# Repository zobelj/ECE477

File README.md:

# Split USB Keyboard
ECE477 Team 4 github

## Reset source code to work as keyboard
1. Make changes to .ioc file and save it
2. Build the code
3. Delete the Middlewares folder
4. Unzip Middlewares KEYBOARD SETUP.zip and rename the folder to Middlewares (Keep the ziped file here for future use)
5. Build the code (there will likely be errors, if so proceed to step 6)
6. Navigate to Drivers>STM32F4xx_HAL_DRIVER>Src in this directory there will be duplicate files that look like this `...cortex.c` and `...cortext 2.c` or `...cortex 3.c` to fix this delete all of the files that have a number at the end of the file name. This can easily be done in the console/terminal with `rm *2.c` or `rm *3.c`

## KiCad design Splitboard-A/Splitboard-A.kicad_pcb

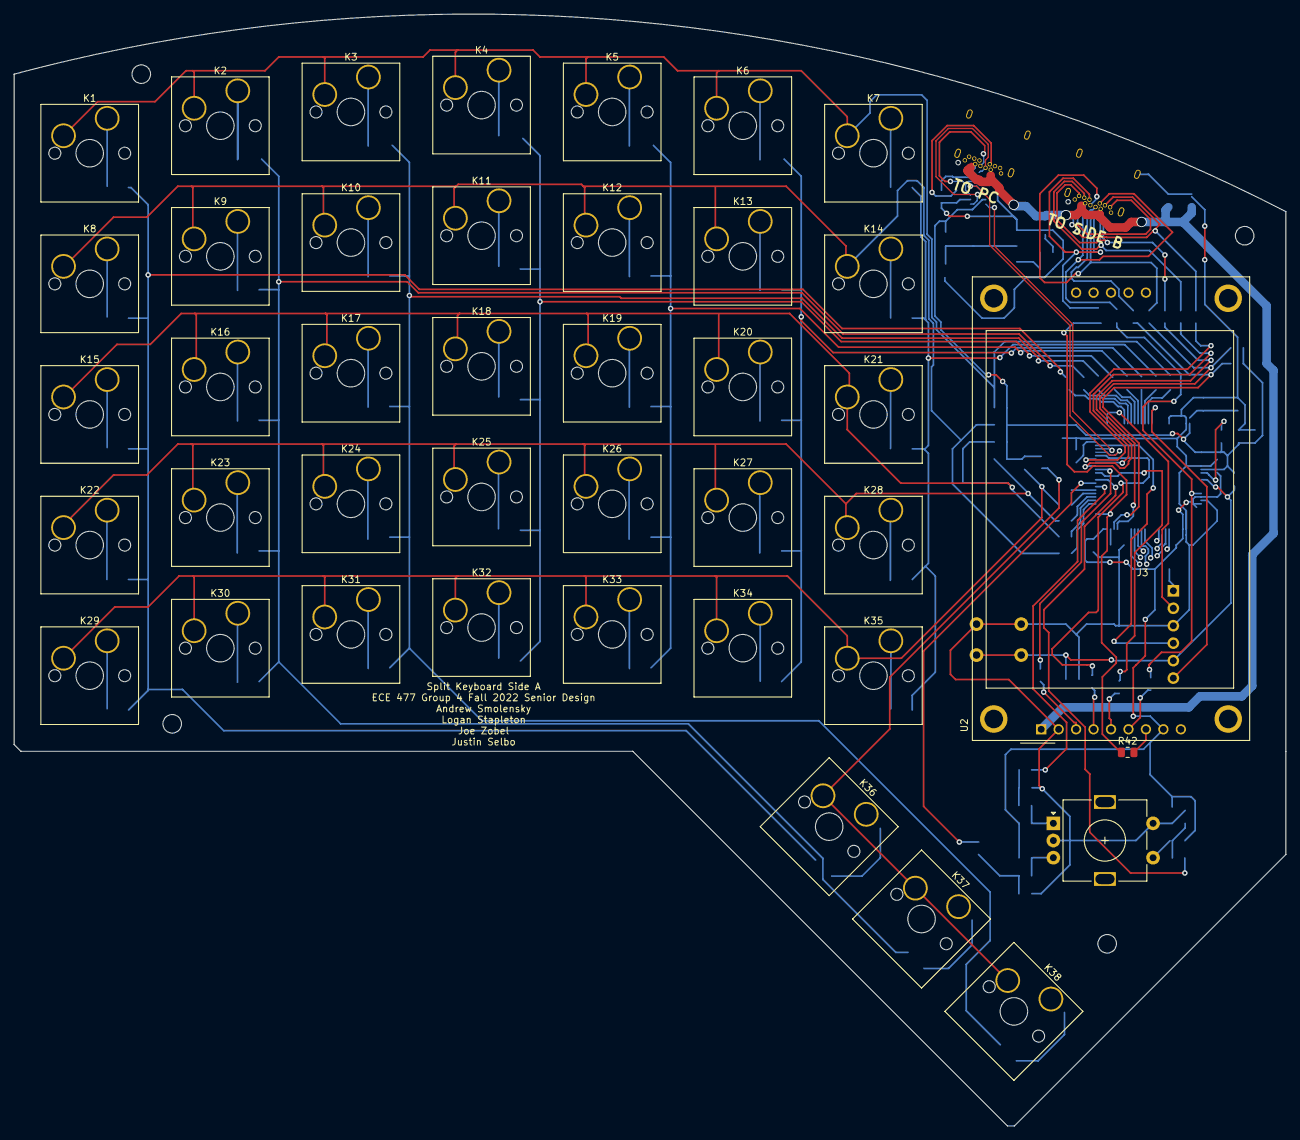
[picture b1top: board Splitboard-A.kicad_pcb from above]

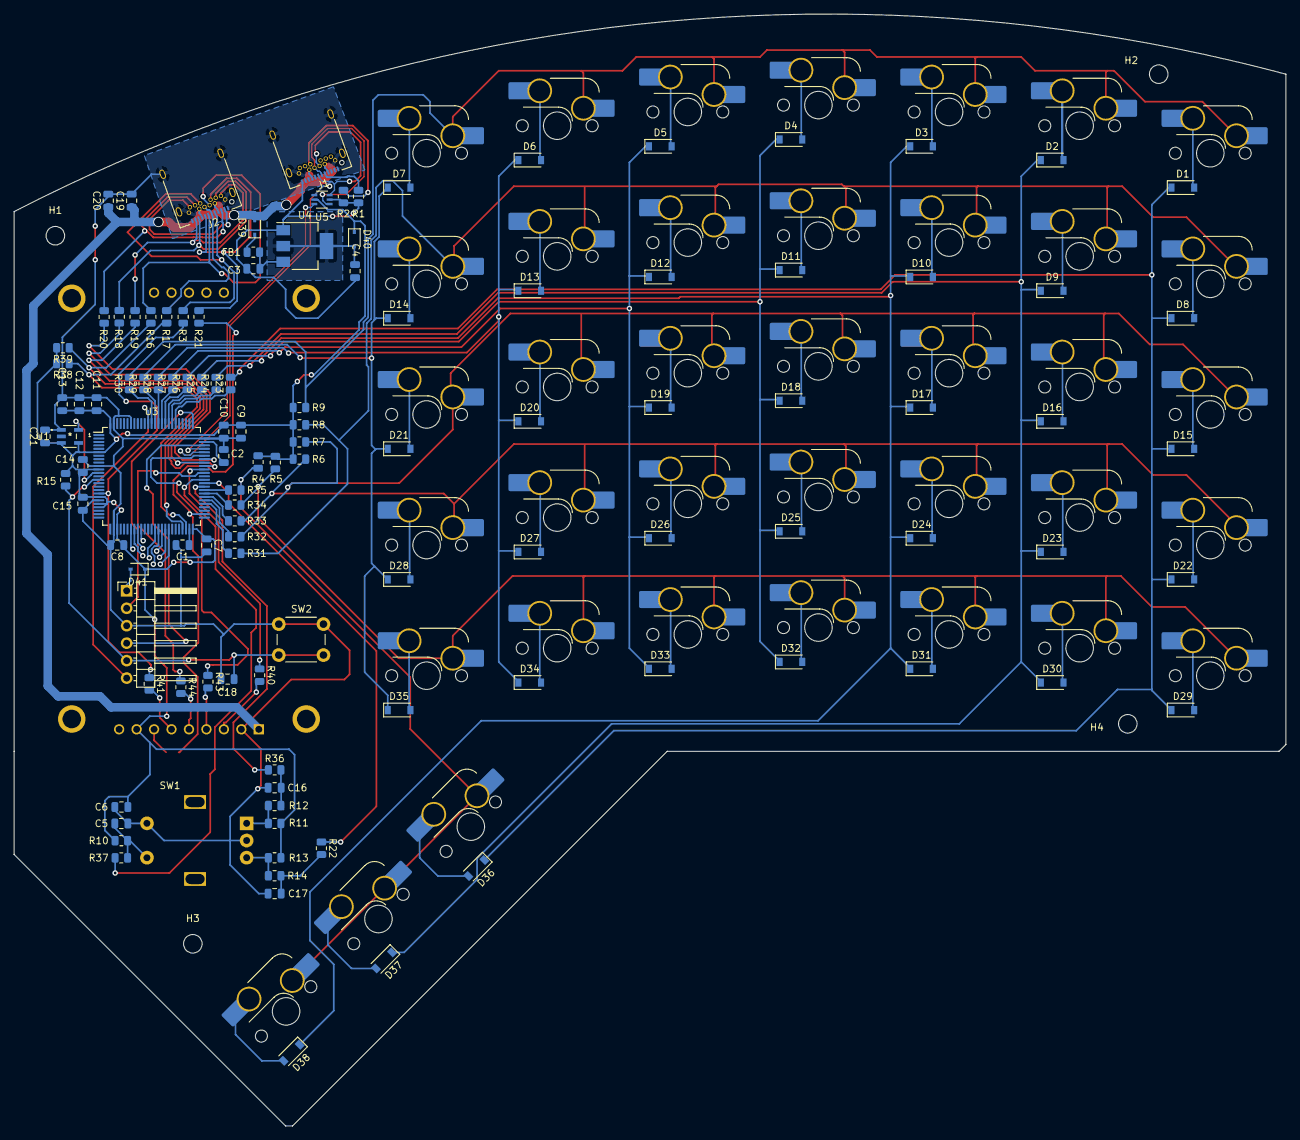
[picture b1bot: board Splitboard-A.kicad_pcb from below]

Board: 2 copper layers, 185.0 x 161.7 mm, 159 parts (118 on the bottom side), 115 nets.

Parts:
C1, C2: 2u2; C_0805_2012Metric
C3, C4: 10u; C_0805_2012Metric
C5, C7, C8, C9, C10, C11, C12, C13, C14, C15, C18, C20, C21: 100nF; C_0805_2012Metric
C6, C19: 10uf; C_0805_2012Metric
C16, C17: .01uF; C_0805_2012Metric
D1, D2, D3, D4, D5, D6, D7, D8, D9, D10, D11, D12, D13, D14, D15, D16, D17, D18, D19, D20, D21, D22, D23, D24, D25, D26, D27, D28, D29, D30, D31, D32, D33, D34, D35, D36, D37, D38: D; D_SOD-123
D39, D40, D41: D_Schottky; D_SOD-323
FB1: 100 @ 100 MHz; R_0805_2012Metric
H1, H2, H3, H4: MountingHole; MountingHole_2.7mm
J1: USB_C_Receptacle_USB2.0; USB_C_Receptacle_Amphenol_12401548E4-2A
J2: USB_C_Receptacle; USB_C_Receptacle_Amphenol_12401548E4-2A
J3: Conn_01x06; PinHeader_1x06_P2.54mm_Horizontal
K1, K2, K3, K4, K5, K6, K7, K8, K9, K10, K11, K12, K13, K14, K15, K16, K17, K18, K19, K20, K21, K22, K23, K24, K25, K26, K27, K28, K29, K30, K31, K32, K33, K34, K35, K36, K37, K38: KEYSW; SW_Hotswap_Kailh_MX_plated
R1, R2: 5K1; R_0805_2012Metric
R3, R16, R17, R18, R19, R20, R21, R22, R23, R24, R25, R26, R27, R28, R29, R30, R31, R32, R33, R34, R35, R36, R37, R40, R41, R42, R43, R44: 20; R_0805_2012Metric
R4, R5, R6, R7, R8, R9, R10, R11, R12, R13, R14: 10k; R_0805_2012Metric
R15: 10K; R_0805_2012Metric
R38, R39: 4k7; R_0805_2012Metric
SW1: RotaryEncoder; RotaryEncoder_Alps_EC11E-Switch_Vertical_H20mm
SW2: SW_Push; SW_PUSH_6mm
U1: SIT2024BA-S2-33E-8.000000G
U2: CR2013-MI2120
U3: STM32F407VGTx; LQFP-100_14x14mm_P0.5mm
U4: AMS1117-3.3; SOT-223-3_TabPin2
U5: USBUF02W6

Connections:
+3.3V: C6.1, C7.1, C8.1, C9.1, C10.1, C11.1, C12.1, C13.1, C14.1, C15.1, C21.1, D40.1 (K), D41.1 (K), R4.2, R5.2, R6.2, R7.2, R8.2, R9.2, R10.2, R11.1, R13.1, R15.1, R38.2, R39.2, U1.3 (OE/NC), U1.4 (VDD), U2.8 (LED), U3.6 (VBAT), U3.11 (VDD), U3.19 (VDD), U3.21 (VREF+), U3.22 (VDDA), U3.28 (VDD), U3.50 (VDD), U3.75 (VDD), U3.100 (VDD), U5.5 (VDD)
/ENC_A: C16.1, R12.1, R36.2
/ENC_B: C17.2, R14.2, R22.2
/ENC_SW: C5.2, R10.1, R37.2, SW1.S1
/LCD1_CS: R40.1, U3.65 (PC8)
/LCD1_DC: R44.1, U3.64 (PC7)
/LCD1_RST: R43.1, U3.69 (PA10)
/LCD2_CS: R18.1, U3.67 (PA8)
/LCD2_DC: R19.1, U3.66 (PC9)
/LCD2_RST: R20.1, U3.68 (PA9)
/MOSI: R3.1, R41.1, U3.18 (PC3)
/NRST: C18.2, J3.5, R15.2, SW2.2, U3.14 (NRST)
/RCC_OSC_IN: U1.5 (OUT), U3.12 (PH0)
/SCK: R21.1, R42.1, U3.52 (PB13)
/SCL: R16.1, R39.1, U3.47 (PB10)
/SDA: R17.1, R38.1, U3.48 (PB11)
/SWCLK: J3.2, U3.76 (PA14)
/SWDIO: J3.4, U3.72 (PA13)
/SWO: J3.6, U3.89 (PB3)
/USB_CONN_D+: J1.A6 (D+), J1.B6 (D+), U5.1 (D1)
/USB_CONN_D-: J1.A7 (D-), J1.B7 (D-), U5.3 (D2)
/USB_D+: U3.71 (PA12), U5.6 (D4)
/USB_D-: U3.70 (PA11), U5.4 (D3)
/col0: K1.1, K2.1, K3.1, K4.1, K5.1, K6.1, K7.1, R9.1, R30.2
/col1: K8.1, K9.1, K10.1, K11.1, K12.1, K13.1, K14.1, R8.1, R31.2
/col2: K15.1, K16.1, K17.1, K18.1, K19.1, K20.1, K21.1, R7.1, R32.2
/col3: K22.1, K23.1, K24.1, K25.1, K26.1, K27.1, K28.1, R6.1, R33.2
/col4: K29.1, K30.1, K31.1, K32.1, K33.1, K34.1, K35.1, R5.1, R34.2
/col5: K36.1, K37.1, K38.1, R4.1, R35.2
/row0: D1.1 (K), D8.1 (K), D15.1 (K), D22.1 (K), D29.1 (K), D36.1 (K), R23.2
/row1: D2.1 (K), D9.1 (K), D16.1 (K), D23.1 (K), D30.1 (K), D37.1 (K), R24.2
/row2: D3.1 (K), D10.1 (K), D17.1 (K), D24.1 (K), D31.1 (K), D38.1 (K), R25.2
/row3: D4.1 (K), D11.1 (K), D18.1 (K), D25.1 (K), D32.1 (K), R26.2
/row4: D5.1 (K), D12.1 (K), D19.1 (K), D26.1 (K), D33.1 (K), R27.2
/row5: D6.1 (K), D13.1 (K), D20.1 (K), D27.1 (K), D34.1 (K), R28.2
/row6: D7.1 (K), D14.1 (K), D21.1 (K), D28.1 (K), D35.1 (K), R29.2
GND: C1.2, C2.2, C3.2, C4.2, C5.1, C6.2, C7.2, C8.2, C9.2, C10.2, C11.2, C12.2, C13.2, C14.2, C15.2, C16.2, C17.1, C18.1, C19.2, C20.2, C21.2, J1.A1 (GND), J1.A12 (GND), J1.B1 (GND), J1.B12 (GND), J1.S1 (SHIELD), J2.A1 (GND), J2.A12 (GND), J2.B1 (GND), J2.B12 (GND), J2.S1 (SHIELD), J3.3, R1.2, R2.2, SW1.C, SW1.S2, SW2.1, U1.1 (GND), U2.2 (GND), U3.10 (VSS), U3.20 (VSSA), U3.27 (VSS), U3.74 (VSS), U3.94 (BOOT0), U3.99 (VSS), U4.1 (GND), U5.2 (GND)
unnamed: C1.1, U3.49 (VCAP_1)
unnamed: C2.1, U3.73 (VCAP_2)
unnamed: C3.1, FB1.2, U4.3 (VI)
unnamed: C4.1, D40.2 (A), U4.2 (VO)
unnamed: D1.2 (A), K1.2
unnamed: D2.2 (A), K2.2
unnamed: D3.2 (A), K3.2
unnamed: D4.2 (A), K4.2
unnamed: D5.2 (A), K5.2
unnamed: D6.2 (A), K6.2
unnamed: D7.2 (A), K7.2
unnamed: D8.2 (A), K8.2
unnamed: D9.2 (A), K9.2
unnamed: D10.2 (A), K10.2
unnamed: D11.2 (A), K11.2
unnamed: D12.2 (A), K12.2
unnamed: D13.2 (A), K13.2
unnamed: D14.2 (A), K14.2
unnamed: D15.2 (A), K15.2
unnamed: D16.2 (A), K16.2
unnamed: D17.2 (A), K17.2
unnamed: D18.2 (A), K18.2
unnamed: D19.2 (A), K19.2
unnamed: D20.2 (A), K20.2
unnamed: D21.2 (A), K21.2
unnamed: D22.2 (A), K22.2
unnamed: D23.2 (A), K23.2
unnamed: D24.2 (A), K24.2
unnamed: D25.2 (A), K25.2
unnamed: D26.2 (A), K26.2
unnamed: D27.2 (A), K27.2
unnamed: D28.2 (A), K28.2
unnamed: D29.2 (A), K29.2
unnamed: D30.2 (A), K30.2
unnamed: D31.2 (A), K31.2
unnamed: D32.2 (A), K32.2
unnamed: D33.2 (A), K33.2
unnamed: D34.2 (A), K34.2
unnamed: D35.2 (A), K35.2
unnamed: D36.2 (A), K36.2
unnamed: D37.2 (A), K37.2
unnamed: D38.2 (A), K38.2
unnamed: D39.1 (K), FB1.1
unnamed: D41.2 (A), J3.1
unnamed: J1.A5 (CC1), R1.1
unnamed: J1.B5 (CC2), R2.1
unnamed: J2.A2 (TX1+), J2.B2 (TX2+)
unnamed: J2.A3 (TX1-), J2.B3 (TX2-), R20.2
unnamed: J2.A5 (CC1), J2.B5 (CC2), R3.2
unnamed: J2.A6 (D+), J2.B6 (D+), R17.2
unnamed: J2.A7 (D-), J2.B7 (D-), R16.2
unnamed: J2.A8 (SBU1), J2.B8 (SBU2), R21.2
unnamed: J2.A10 (RX2-), J2.B10 (RX1-), R18.2
unnamed: J2.A11 (RX2+), J2.B11 (RX1+), R19.2
unnamed: R11.2, R12.2, SW1.A
unnamed: R13.2, R14.1, SW1.B
unnamed: R22.1, U3.61 (PD14)
unnamed: R23.1, U3.81 (PD0)
unnamed: R24.1, U3.82 (PD1)
unnamed: R25.1, U3.83 (PD2)
unnamed: R26.1, U3.84 (PD3)
unnamed: R27.1, U3.85 (PD4)
unnamed: R28.1, U3.86 (PD5)
unnamed: R29.1, U3.87 (PD6)
unnamed: R30.1, U3.88 (PD7)
unnamed: R31.1, U3.55 (PD8)
unnamed: R32.1, U3.56 (PD9)
unnamed: R33.1, U3.57 (PD10)
unnamed: R34.1, U3.58 (PD11)
unnamed: R35.1, U3.59 (PD12)
unnamed: R36.1, U3.60 (PD13)
unnamed: R37.1, U3.62 (PD15)
unnamed: R40.2, U2.3 (~CS)
unnamed: R43.2, U2.4 (RESET)
unnamed: R44.2, U2.5 (D/~C)
unnamed: R41.2, U2.6 (MOSI)
unnamed: R42.2, U2.7 (SCK)
VBUS: C19.1, C20.1, D39.2 (A), J1.A4 (VBUS), J1.A9 (VBUS), J1.B4 (VBUS), J1.B9 (VBUS), J2.A4 (VBUS), J2.A9 (VBUS), J2.B4 (VBUS), J2.B9 (VBUS), U2.1 (VCC)

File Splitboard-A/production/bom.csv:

Designator,Footprint,Quantity,Value,LCSC Part #
"C1, C2",C_0805_2012Metric,2,2u2,
"C10, C11, C12, C13, C14, C15, C18, C20, C21, C5, C7, C8, C9",C_0805_2012Metric,13,100nF,
"C16, C17",C_0805_2012Metric,2,.01uF,
"C19, C6",C_0805_2012Metric,2,10uf,
"C3, C4",C_0805_2012Metric,2,10u,
"D1, D10, D11, D12, D13, D14, D15, D16, D17, D18, D19, D2, D20, D21, D22, D23, D24, D25, D26, D27, D28, D29, D3, D30, D31, D32, D33, D34, D35, D36, D37, D38, D4, D5, D6, D7, D8, D9",D_SOD-123,38,D,
"D39, D40, D41",D_SOD-123,3,D_Schottky,
FB1,R_0805_2012Metric,1,100 @ 100 MHz,
"H1, H2, H3, H4",MountingHole_2.7mm,4,MountingHole,
J1,USB_C_Receptacle_Amphenol_12401548E4-2A,1,USB_C_Receptacle_USB2.0,
J2,USB_C_Receptacle_Amphenol_12401548E4-2A,1,USB_C_Receptacle,
J3,PinHeader_1x06_P2.54mm_Horizontal,1,Conn_01x06,
"K1, K10, K11, K12, K13, K14, K15, K16, K17, K18, K19, K2, K20, K21, K22, K23, K24, K25, K26, K27, K28, K29, K3, K30, K31, K32, K33, K34, K35, K36, K37, K38, K4, K5, K6, K7, K8, K9",SW_Hotswap_Kailh_MX_plated,38,KEYSW,
"R1, R2",R_0805_2012Metric,2,5K1,
"R10, R11, R12, R13, R14, R15, R4, R5, R6, R7, R8, R9",R_0805_2012Metric,12,10k,
"R16, R17, R18, R19, R20, R21, R22, R23, R24, R25, R26, R27, R28, R29, R3, R30, R31, R32, R33, R34, R35, R36, R37",R_0805_2012Metric,23,20,
"R38, R39",R_0805_2012Metric,2,4k7,
SW1,RotaryEncoder_Alps_EC11E-Switch_Vertical_H20mm,1,RotaryEncoder,
SW2,SW_PUSH_6mm,1,SW_Push,
U1,SIT2024BA-S2-33E-8.000000G,1,SIT2024BA-S2-33E-8.000000G,
U2,CR2013-MI2120,1,CR2013-MI2120,
U3,LQFP-100_14x14mm_P0.5mm,1,STM32F407VGTx,
U4,SOT-223-3_TabPin2,1,AMS1117-3.3,
U5,USBUF02W6,1,USBUF02W6,

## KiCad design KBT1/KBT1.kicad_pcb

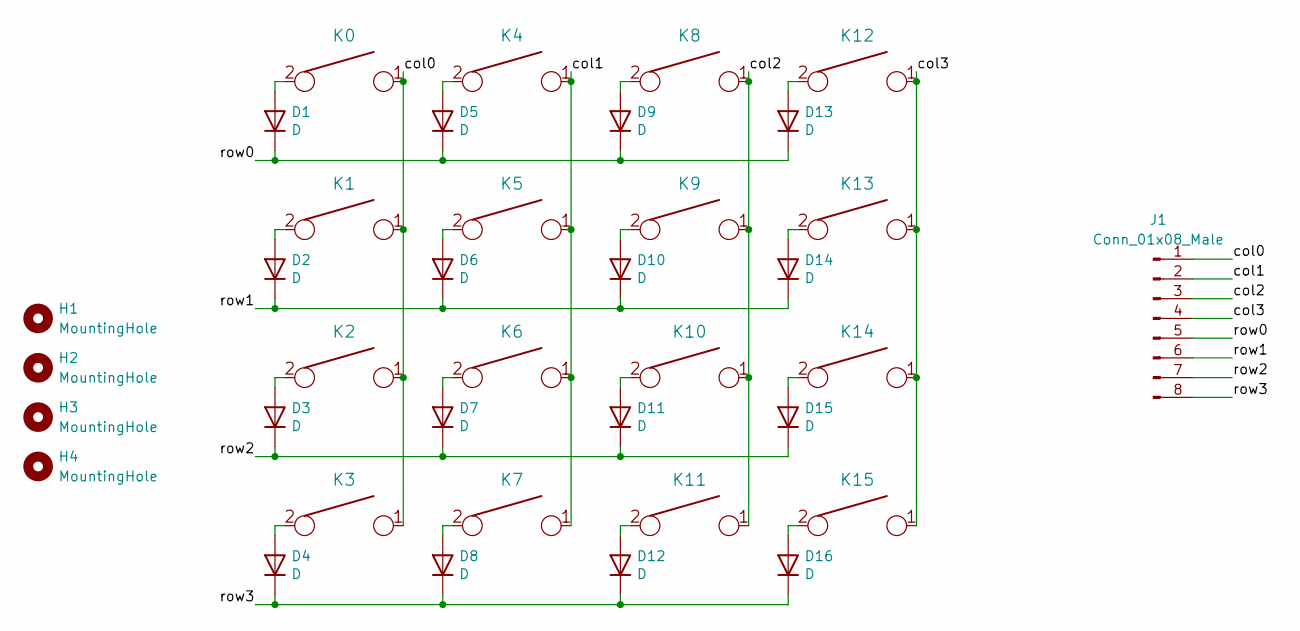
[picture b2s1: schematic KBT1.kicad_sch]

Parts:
D1, D2, D3, D4, D5, D6, D7, D8, D9, D10, D11, D12, D13, D14, D15, D16: D; D_DO-35_SOD27_P7.62mm_Horizontal
H1, H2, H3, H4: MountingHole; MountingHole_2.7mm
J1: Conn_01x08_Male; PinHeader_1x08_P2.54mm_Vertical
K0, K1, K2, K3, K4, K5, K6, K7, K8, K9, K10, K11, K12, K13, K14, K15: KEYSW; SW_Hotswap_Kailh_MX_plated

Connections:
/col0: J1.1, K0.1, K1.1, K2.1, K3.1
/col1: J1.2, K4.1, K5.1, K6.1, K7.1
/col2: J1.3, K8.1, K9.1, K10.1, K11.1
/col3: J1.4, K12.1, K13.1, K14.1, K15.1
/row0: D1.1 (K), D5.1 (K), D9.1 (K), D13.1 (K), J1.5
/row1: D2.1 (K), D6.1 (K), D10.1 (K), D14.1 (K), J1.6
/row2: D3.1 (K), D7.1 (K), D11.1 (K), D15.1 (K), J1.7
/row3: D4.1 (K), D8.1 (K), D12.1 (K), D16.1 (K), J1.8
unnamed: D1.2 (A), K0.2
unnamed: D2.2 (A), K1.2
unnamed: D3.2 (A), K2.2
unnamed: D4.2 (A), K3.2
unnamed: D5.2 (A), K4.2
unnamed: D6.2 (A), K5.2
unnamed: D7.2 (A), K6.2
unnamed: D8.2 (A), K7.2
unnamed: D9.2 (A), K8.2
unnamed: D10.2 (A), K9.2
unnamed: D11.2 (A), K10.2
unnamed: D12.2 (A), K11.2
unnamed: D13.2 (A), K12.2
unnamed: D14.2 (A), K13.2
unnamed: D15.2 (A), K14.2
unnamed: D16.2 (A), K15.2

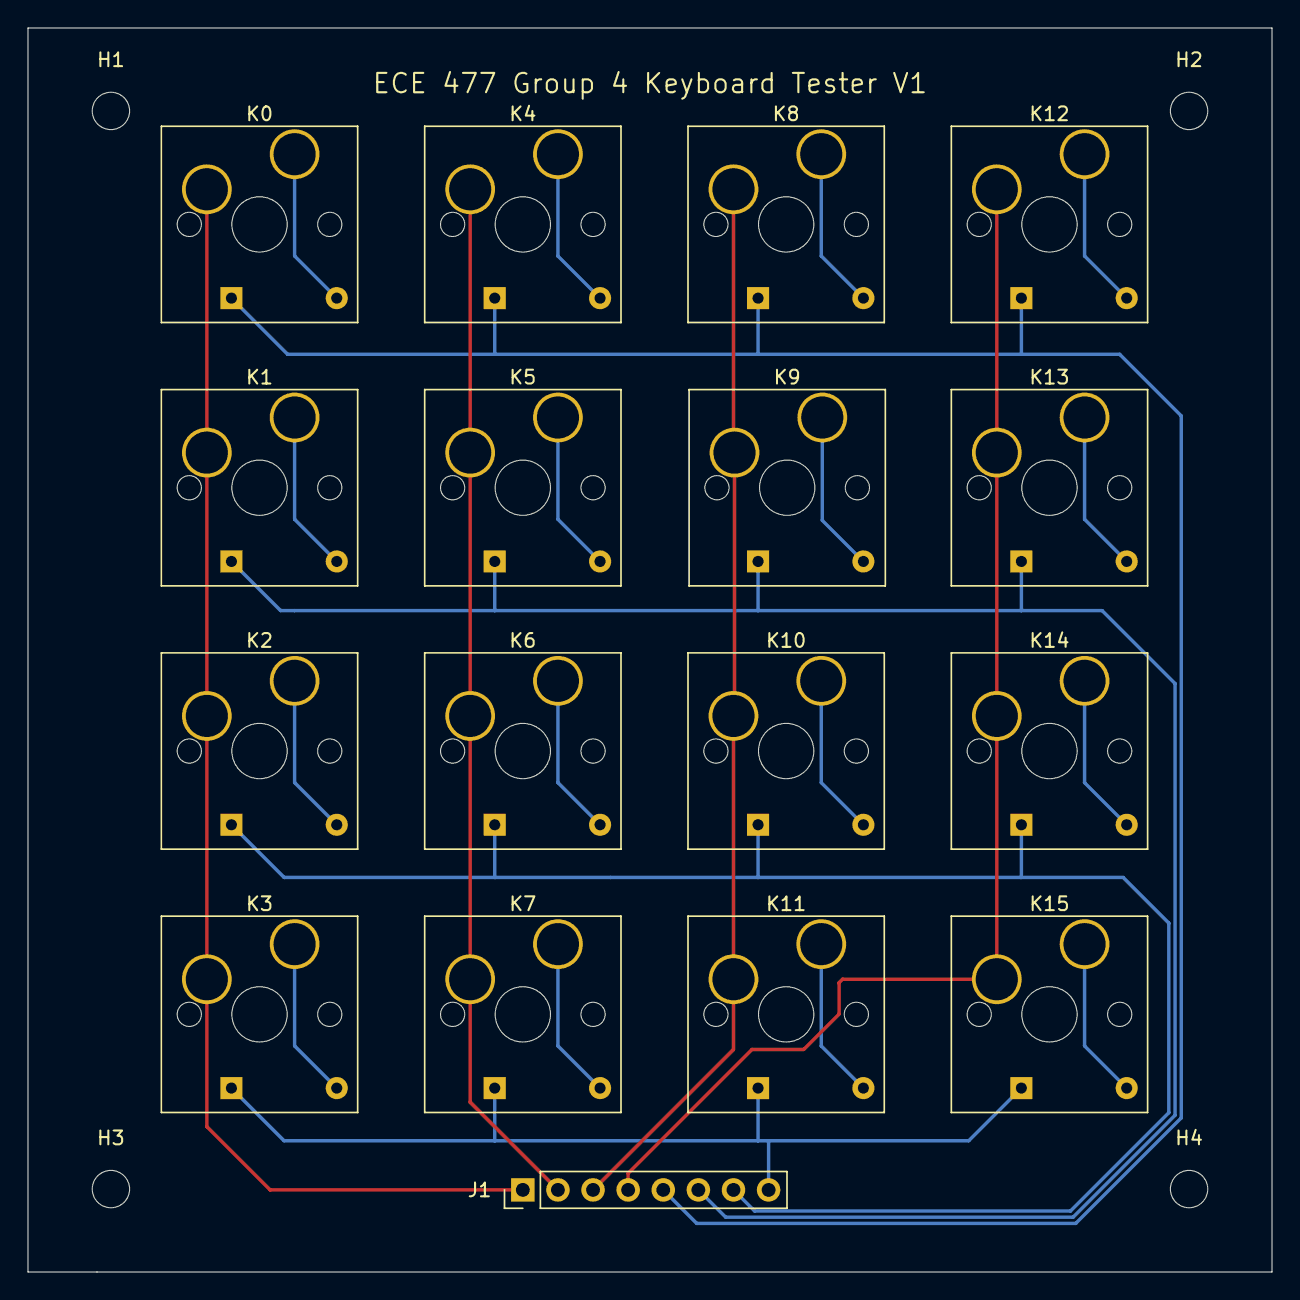
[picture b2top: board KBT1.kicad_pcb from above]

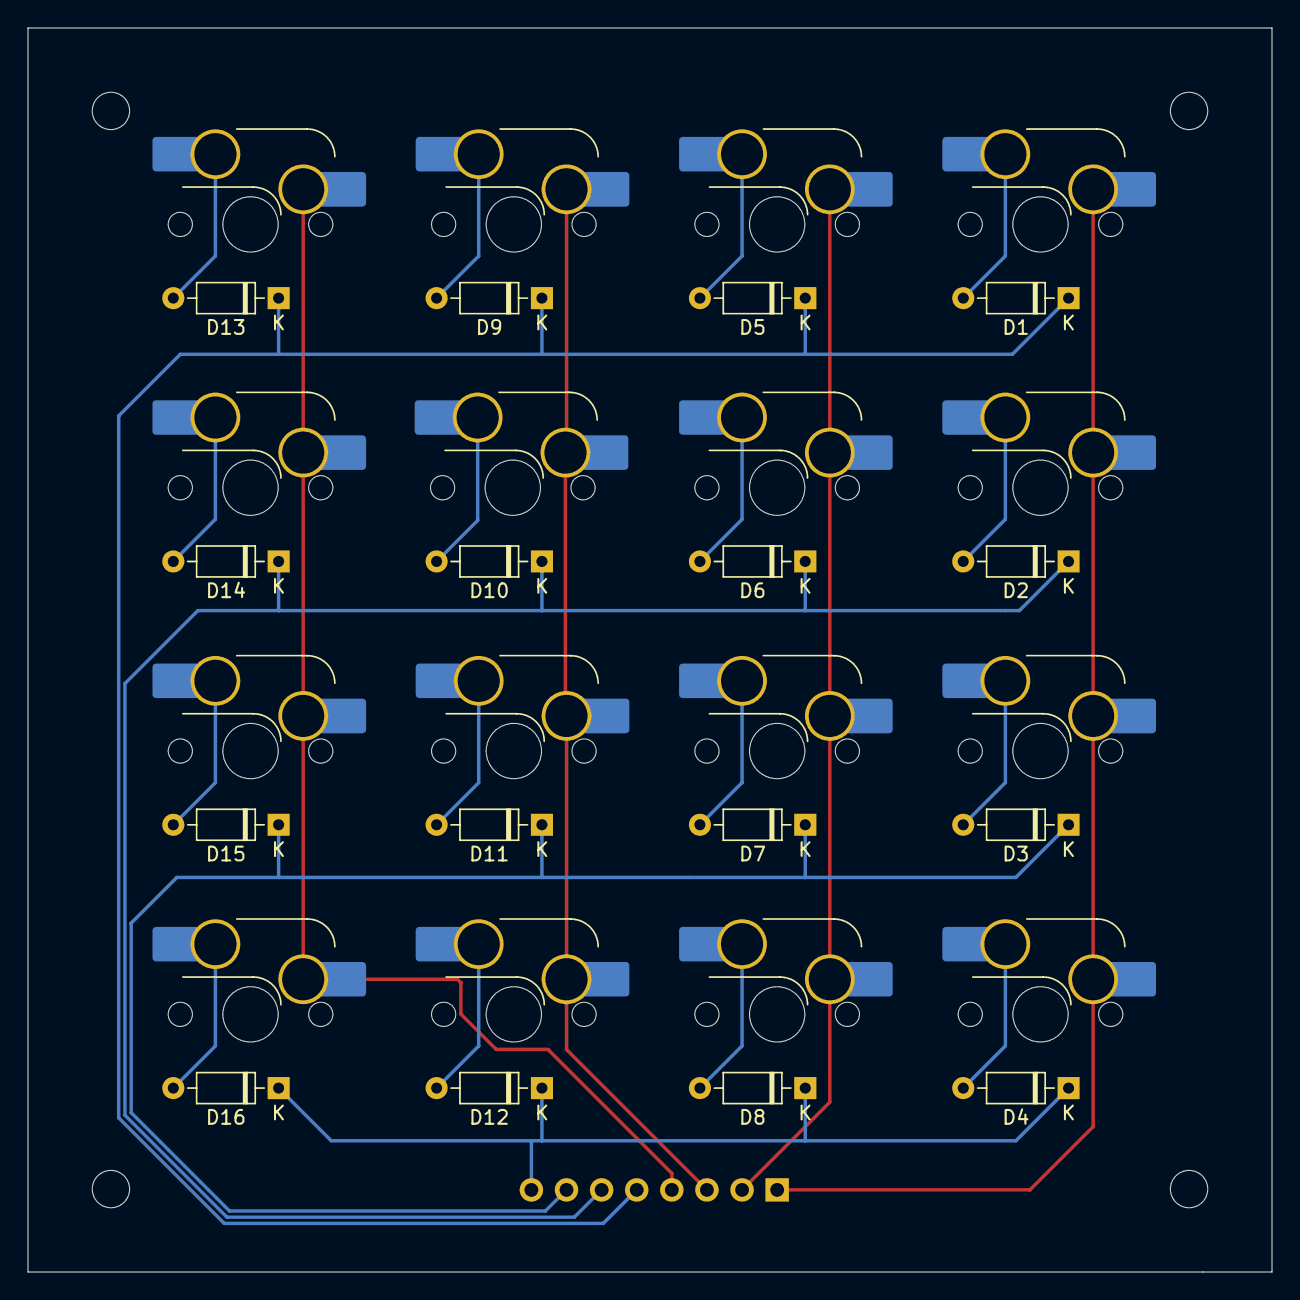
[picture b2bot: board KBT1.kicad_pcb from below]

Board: 2 copper layers, 90.0 x 90.0 mm, 37 parts (16 on the bottom side), 24 nets.

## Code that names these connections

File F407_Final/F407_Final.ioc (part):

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Mcu.Name=STM32F407V(E-G)Tx
Mcu.Package=LQFP100
Mcu.UserName=STM32F407VGTx
PA10.GPIOParameters=GPIO_Label
PA10.GPIO_Label=LCD1_RST
PA10.Signal=GPIO_Output
PA11.Mode=Device_Only
PA11.Signal=USB_OTG_FS_DM
PA12.Mode=Device_Only
PA12.Signal=USB_OTG_FS_DP
PA13.Mode=Serial_Wire
PA13.Signal=SYS_JTMS-SWDIO
PA14.Mode=Serial_Wire
PA14.Signal=SYS_JTCK-SWCLK
PA8.GPIOParameters=GPIO_Label
PA8.GPIO_Label=LCD2_CS
PA8.Signal=GPIO_Output
PA9.GPIOParameters=GPIO_Label
PA9.GPIO_Label=LCD2_RST
PA9.Signal=GPIO_Output
PB10.Mode=I2C
PB10.Signal=I2C2_SCL
PB11.Mode=I2C
PB11.Signal=I2C2_SDA
PB13.Mode=TX_Only_Simplex_Unidirect_Master
PB13.Signal=SPI2_SCK
PC3.Mode=TX_Only_Simplex_Unidirect_Master
PC3.Signal=SPI2_MOSI
PC7.GPIOParameters=GPIO_Label
PC7.GPIO_Label=LCD1_DC
PC7.Signal=GPIO_Output
PC8.GPIOParameters=GPIO_Label
PC8.GPIO_Label=LCD1_CS
PC8.Signal=GPIO_Output
PC9.GPIOParameters=GPIO_Label
PC9.GPIO_Label=LCD2_DC
PC9.Signal=GPIO_Output
PD0.GPIOParameters=GPIO_Label
PD0.GPIO_Label=ROW0
PD0.Signal=GPIO_Output
PD1.GPIOParameters=GPIO_Label
PD1.GPIO_Label=ROW1
PD1.Signal=GPIO_Output
PD10.GPIOParameters=GPIO_Label
PD10.GPIO_Label=COL3
PD10.Signal=GPIO_Input
PD11.GPIOParameters=GPIO_Label
PD11.GPIO_Label=COL4
PD11.Signal=GPIO_Input
PD12.GPIOParameters=GPIO_Label
PD12.GPIO_Label=COL5
PD12.Signal=GPIO_Input
PD13.GPIOParameters=GPIO_Label
PD13.GPIO_Label=ENC_A
PD13.Signal=GPIO_Input
PD14.GPIOParameters=GPIO_Label
PD14.GPIO_Label=ENC_B
PD14.Signal=GPIO_Input
PD15.GPIOParameters=GPIO_Label
PD15.GPIO_Label=ENC_SW
PD15.Signal=GPIO_Input
PD2.GPIOParameters=GPIO_Label
PD2.GPIO_Label=ROW2
PD2.Signal=GPIO_Output
PD3.GPIOParameters=GPIO_Label
PD3.GPIO_Label=ROW3
PD3.Signal=GPIO_Output
PD4.GPIOParameters=GPIO_Label
PD4.GPIO_Label=ROW4
PD4.Signal=GPIO_Output
PD5.GPIOParameters=GPIO_Label
PD5.GPIO_Label=ROW5
PD5.Signal=GPIO_Output
PD6.GPIOParameters=GPIO_Label
PD6.GPIO_Label=ROW6
PD6.Signal=GPIO_Output
PD7.GPIOParameters=GPIO_Label
PD7.GPIO_Label=COL0
PD7.Signal=GPIO_Input
PD8.GPIOParameters=GPIO_Label
PD8.GPIO_Label=COL1
PD8.Signal=GPIO_Input
PD9.GPIOParameters=GPIO_Label
PD9.GPIO_Label=COL2
PD9.Signal=GPIO_Input
PH0-OSC_IN.Mode=HSE-External-Clock-Source
PH0-OSC_IN.Signal=RCC_OSC_IN
PH1-OSC_OUT.Mode=HSE-External-Clock-Source
PH1-OSC_OUT.Signal=RCC_OSC_OUT
RCC.HSE_Timout=1000
RCC.HSE_VALUE=8000000
RCC.SYSCLKFreq_VALUE=72000000
RCC.SYSCLKSource=RCC_SYSCLKSOURCE_PLLCLK
board=custom

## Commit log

2022-08-31 Added datasheets folder & stm32f303 reference pdf
2022-08-31 created readme
2022-09-06 added pcb files
2022-09-08 added preliminary software outline
2022-09-08 added STM32F091 workspace
2022-09-08 removed test workspace
2022-09-09 keyboard tester initial work
2022-09-09 added board outline, added missing trace
2022-09-09 screenshots
2022-09-09 increased header size
2022-09-09 added wpm POC
2022-09-09 added stm32f407 documentation
2022-09-12 .DS_Store banished
2022-09-13 new diode footprint, added mounting holes
2022-09-13 created gerbers for pcb
2022-09-13 added stm32f091 documentation
2022-09-15 added gpio expanded datasheet
2022-09-15 Created esd protection & Voltage regulation schematics
2022-09-15 Added voltage regulator datasheet
2022-09-16 added stm32f407 errata
2022-09-20 Final project schematic initial commit
2022-09-20 added F407 rotary code for the CubeIDE
2022-09-23 Added Diode datasheet
2022-09-23 kicad backups
2022-09-27 created 3d model for the keyboard as well as kbt1 acrylic models
2022-09-27 added note about wiring the keypad
2022-09-27 added workspace for current prototype
2022-09-27 added lcd & stm32 usb documentation
2022-09-28 Keyboard changes (added split to other half, component footprints)
2022-09-29 added volume control, added keycodes.h
2022-09-29 added pullup resisitors
2022-09-30 started working on I2C
2022-09-30 Schematic modifications
2022-09-30 Schematic changes, linked both boards under a new project
2022-09-30 Schema changes
2022-09-30 i2c scanning working
2022-09-30 fixed secondary keyboard layout
2022-10-01 Schema changes (rotary encoder, debug header)
2022-10-01 added code flowchart
2022-10-02 updated some pins and net labels on sba
2022-10-02 Halved tim6 frequency increased i2c speed to 400kHz
2022-10-03 Updated readme with keyboard reset procedures
2022-10-03 Layout changes
2022-10-03 got both screens working
2022-10-04 lcd screens working with keypads
2022-10-04 metadata changes
2022-10-04 Side A layout updates
2022-10-04 keyboard layout changes
2022-10-04 layout updates
2022-10-05 Added switch footprint (6x6mm)
2022-10-05 added mcp23017 datasheet
2022-10-05 cleaned datasheet folder
2022-10-05 Added Joe's suggestions & notes to schematic & pcb
2022-10-06 updated USB, LCD, ESD, Voltage Reg in schematic
2022-10-06 keypad, i2c, and lcds working together
2022-10-06 assigned new component footprints
2022-10-06 splitboard A backup
2022-10-06 Added debugging header to splitboard B
2022-10-06 Splitboard B schematic completed, added some additional notes on board A
2022-10-10 Routing PCB
2022-10-10 created archive zip files
2022-10-11 Splitboard A schematic completed (added mosi and sck)
2022-10-12 Cleanup
2022-10-13 added more archive files
2022-10-18 shift key, rotary counter on LCD1
2022-10-18 Updated Schematics with suggestions from course staff
2022-10-22 Addes rseries for LCD and added extra vias
2022-11-01 wpm working
2022-11-02 archive file save
2022-11-08 added fonts
2022-11-08 fixed display
2022-11-11 added keyswitch datasheet
2022-11-11 project for final PCB
2022-11-11 added laser files
2022-11-13 row-col scanning working on lab computer and final pcb
2022-11-14 Started I2c code
2022-11-14 merged logan's I2C changes with my updated layout changes
2022-11-14 cleaned up logic for modifier keys, added primary rotary encoder functionality
2022-11-15 added expander row-col scanning and rotary encoder scanning
2022-11-15 not working?
2022-11-15 Fixed LCD switch function
    compared the DC pin values because they are on different pin numbers (different enumeration values)
2022-11-15 added switch_lcd fix
2022-11-15 added fonts.c changes
2022-11-15 fixed undefined keypresses2 errors
2022-11-16 lcds finished?
2022-11-17 row-col scanning w/ entire column issue
2022-11-17 pushing IOC file
2022-12-06 working final changes I forgot to push

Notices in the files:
parts and their libraries:
Copyright 2021 Accelerated Designs. All rights reserved.
